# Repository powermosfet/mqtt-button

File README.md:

MQTT button
===========

# A generic IoT device

This repo contains KiCad design files and lua code for an IoT box with the following:

* Two pushbuttons
* Two LED's
* an AM2320 temperature- and humidity sensor

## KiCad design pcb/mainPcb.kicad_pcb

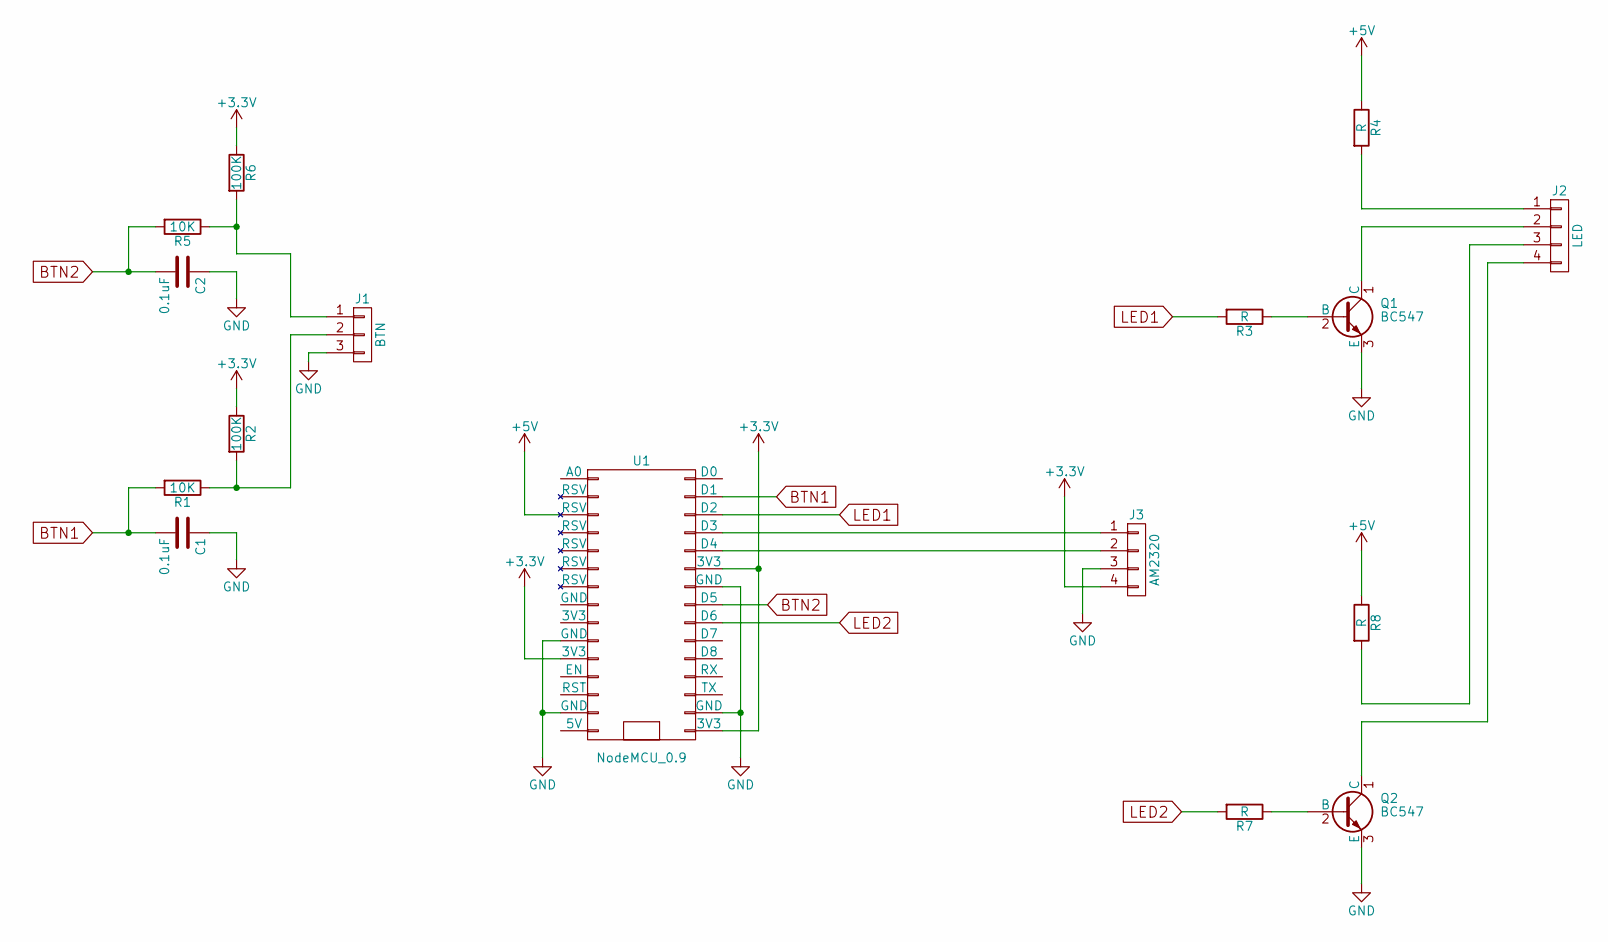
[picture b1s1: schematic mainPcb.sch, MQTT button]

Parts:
C1, C2: 0.1uF; C_Axial_L3.8mm_D2.6mm_P7.50mm_Horizontal
J1: BTN; JST_EH_B03B-EH-A_03x2.50mm_Straight
J2: LED; JST_EH_B04B-EH-A_04x2.50mm_Straight
J3: AM2320; JST_EH_B04B-EH-A_04x2.50mm_Straight
Q1, Q2: BC547; TO-92_Molded_Narrow
R1, R5: 10K; R_Axial_DIN0204_L3.6mm_D1.6mm_P7.62mm_Horizontal
R2, R6: 100K; R_Axial_DIN0204_L3.6mm_D1.6mm_P7.62mm_Horizontal
R3, R4, R7, R8: R; R_Axial_DIN0204_L3.6mm_D1.6mm_P7.62mm_Horizontal
U1: NodeMCU_0.9; NodeMCU_LoLin_V3

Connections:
+3V3: J3.4, R2.1, R6.1, U1.11 (3V3), U1.16 (3V3), U1.25 (3V3)
+5V: R4.1, R8.1, U1.3 (RSV)
BTN1: C1.2, R1.2, U1.29 (D1)
BTN2: C2.2, R5.2, U1.23 (D5)
GND: C1.1, C2.1, J1.3, J3.3, Q1.3 (E), Q2.3 (E), U1.10 (GND), U1.14 (GND), U1.17 (GND), U1.24 (GND)
LED1: R3.2, U1.28 (D2)
LED2: R7.2, U1.22 (D6)
unnamed: J1.1, R5.1, R6.2
unnamed: J1.2, R1.1, R2.2
unnamed: J2.1, R4.2
unnamed: J2.2, Q1.1 (C)
unnamed: J2.3, R8.2
unnamed: J2.4, Q2.1 (C)
unnamed: J3.1, U1.27 (D3)
unnamed: J3.2, U1.26 (D4)
unnamed: Q1.2 (B), R3.1
unnamed: Q2.2 (B), R7.1

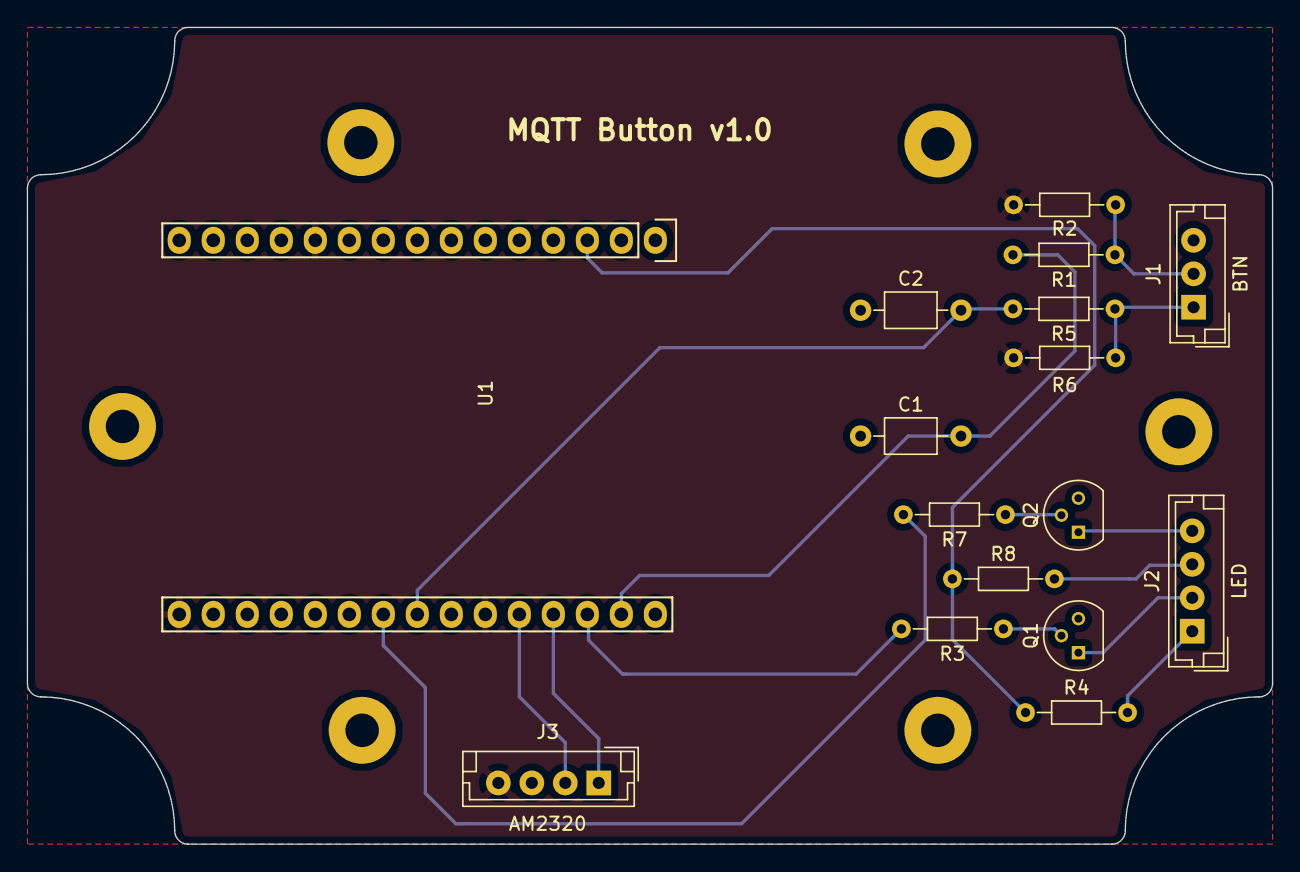
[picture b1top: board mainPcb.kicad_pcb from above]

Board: 2 copper layers, 93.0 x 61.0 mm, 16 parts (0 on the bottom side), 17 nets.

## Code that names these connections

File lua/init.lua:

local wifiSetup = require("wifiSetup")
local config    = require("config")
local button    = require("button")
local led       = require("led")

local pubTimer = tmr.create()
local mqttCli  = mqtt.Client(config.mqttClientName, config.mqttClientTimeout)
local btn1     = button.create(config.board.pinButton1, mqttCli, config.mqttTopicButton1)
local btn2     = button.create(config.board.pinButton2, mqttCli, config.mqttTopicButton2)
local led1     = led.create(config.board.pinLed1)
local led2     = led.create(config.board.pinLed2)

am2320.init(config.board.pinAm2320Sda, config.board.pinAm2320Scl)

function invert(old)
   if old == gpio.LOW then
      return gpio.HIGH
   else
      return gpio.LOW
   end
end

function msecs(time)
   return ((time.hours * 60 + time.minutes) * 60 + time.seconds) * 1000
end

function main()
   mqttCli:on("connect", function(client) print ("connected") end)
   mqttCli:on("offline", function(client) print ("offline") end)

   print("MQTT connecting")
   mqttCli:connect(config.mqttServerHost, config.mqttServerPort, 0, function(client)
      print("MQTT connected")

      client:subscribe(config.mqttTopicBase .. config.mqttTopicLed1, 0, function(conn)
         print("subscribe to LED1 success")

         client:subscribe(config.mqttTopicBase .. config.mqttTopicLed2, 0, function(conn)
            print("subscribe to LED2 success")
         end)
      end)

      client:on("message", function(client, topic, message)
         if topic == config.mqttTopicBase .. config.mqttTopicLed1 then
            if message == "1" then
               led1.on()
            else
               led1.off()
            end
         end

         if topic == config.mqttTopicBase .. config.mqttTopicLed2 then
            if message == "1" then
               led2.on()
            else
               led2.off()
            end
         end
      end)

      -- temp/humidity timer
      pubTimer:alarm(msecs(config.am2320Interval), tmr.ALARM_AUTO, function()
         local rh = 0
         local t = 0
         rh, t = am2320.read()
         client:publish(config.mqttTopicBase .. "temperature", t / 10, 0, 0)
         print("Publishing temp: " .. t / 10)
         client:publish(config.mqttTopicBase .. "humidity", rh / 10, 0, 0)
         print("Publishing humidity: " .. rh / 10)
      end)
   end)
end

-- Setup
wifi.setmode(wifi.STATION)
wifi.sta.autoconnect(1)

-- Check for "setup" button
button1Value = gpio.read(config.board.pinButton1)
button2Value = gpio.read(config.board.pinButton2)
if button1Value == gpio.LOW and button2Value == gpio.LOW then
   wifiSetup.enter_setup(main)

else
   print("Performing normal startup...")
   print("Current WiFi status: " .. wifi.sta.status())
   if wifi.sta.status() == wifi.STA_GOTIP then
         print("Got IP. starting main...")
      main()

   else
      print("No ip. waiting...")
      wifi.sta.eventMonReg(wifi.STA_GOTIP, function()
         print("Got IP. starting main...")
         main()
      end)
   end
end

wifi.sta.eventMonStart()

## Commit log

2017-07-20 Add README.md
2017-07-21 Split functionality into modules
